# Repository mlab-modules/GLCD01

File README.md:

# GLCD01 - MIP LCD display module

MLAB module for the [TN0181ANVNANN-GN00](doc/datasheets/MIP_LCD.pdf) square MIP (Memory-in-Pixel) LCD display. MIP displays retain the image without power, making them suitable for low-power applications. The display is connected via a 10-pin FPC connector (J2) and communicates over a 3-wire SPI interface (SCLK, SI, SCS).

The module includes a [MIC1557](https://www.microchip.com/en-us/product/mic1557) RC oscillator that generates the required VCOM polarity-reversal signal for the LCD, so no external signal source is needed. Power supply is 3.3 V via the standard MLAB 2×7 pin header (J1).

## Design

## Schematics

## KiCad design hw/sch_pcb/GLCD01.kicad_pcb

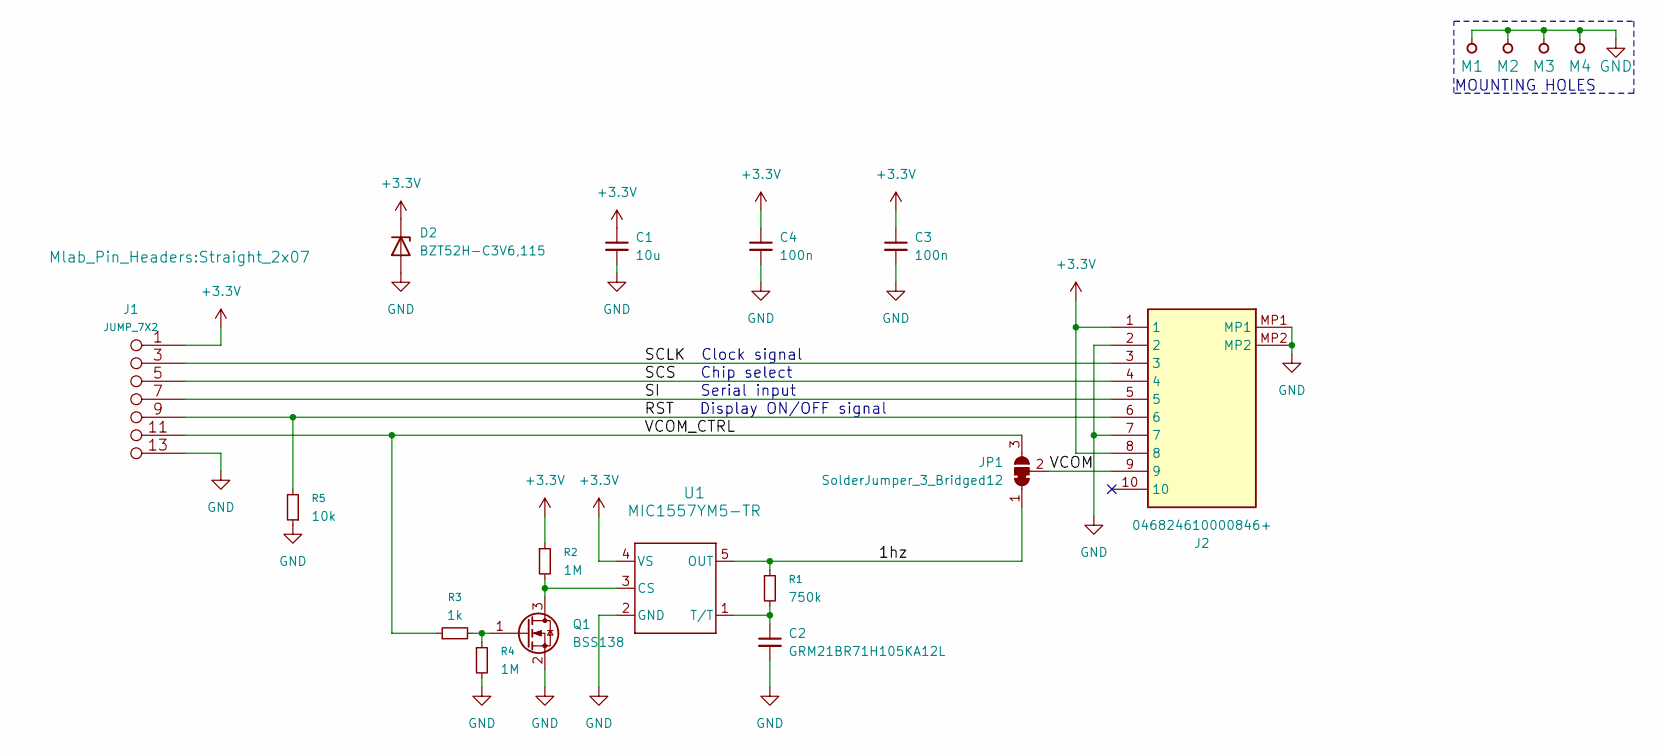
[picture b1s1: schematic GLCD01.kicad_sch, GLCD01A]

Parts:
C1: 10u; C_0603_1608Metric
C2: GRM21BR71H105KA12L; C_0603_1608Metric
C3, C4: 100n; C_0603_1608Metric
D2: BZT52H-C3V6,115; D_SOD-123F
J1: JUMP_7X2; Straight_2x07
J2: 046824610000846+; 046824610000846; Mouser Part Number 346-046824610000846
JP1: SolderJumper_3_Bridged12; SolderJumper-3_P1.3mm_Bridged12_RoundedPad1.0x1.5mm
M1, M2: HOLE M3; MountingHole_3mm
M3, M4: HOLE; MountingHole_3mm
Q1: BSS138; SOT-23
R1: 750k; R_0603_1608Metric
R2, R4: 1M; R_0603_1608Metric
R3: 1k; R_0603_1608Metric
R5: 10k; R_0603_1608Metric
U1: MIC1557YM5-TR; SOT-23-5

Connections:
+3.3V: C1.1, C3.1, C4.1, D2.1 (K), J1.1 (2), J1.2, J2.1, J2.8, R2.1, U1.4 (VS)
/1hz: JP1.1 (A), R1.1, U1.5 (OUT)
/RST: J1.9 (10), J1.10, J2.6, R5.2
/SCLK: J1.3 (4), J1.4, J2.3
/SCS: J1.5 (6), J1.6, J2.4
/SI: J1.7 (8), J1.8, J2.5
/VCOM: J2.9, JP1.2 (C)
/VCOM_CTRL: J1.11 (12), J1.12, JP1.3 (B), R3.1
GND: C1.2, C2.2, C3.2, C4.2, D2.2 (A), J1.13 (14), J1.14, J2.2, J2.7, J2.MP1, J2.MP2, M1.1, M2.1, M3.1, M4.1, Q1.2 (S), R4.2, R5.1, U1.2 (GND)
unnamed: Q1.3 (D), R2.2, U1.3 (CS)
unnamed: Q1.1 (G), R3.2, R4.1
unnamed: C2.1, R1.2, U1.1 (T/T)

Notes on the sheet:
Display ON/OFF signal
Clock signal
MOUNTING HOLES
Serial input
Chip select

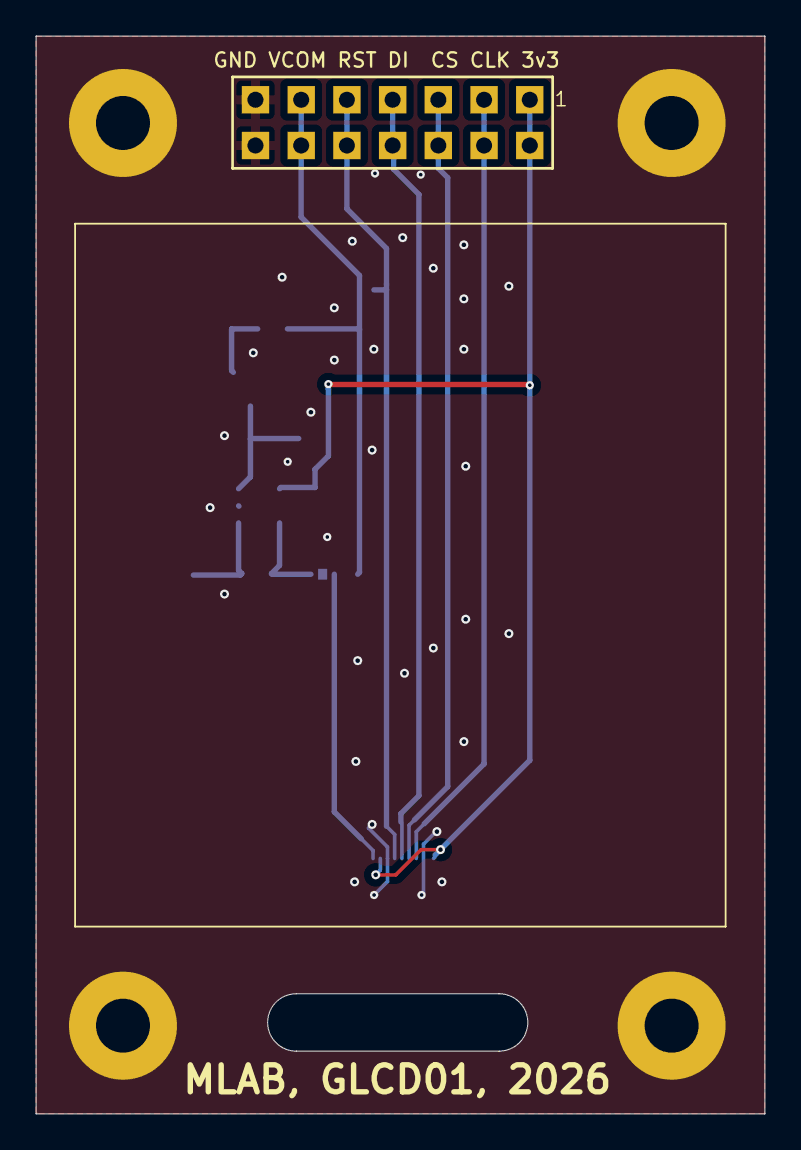
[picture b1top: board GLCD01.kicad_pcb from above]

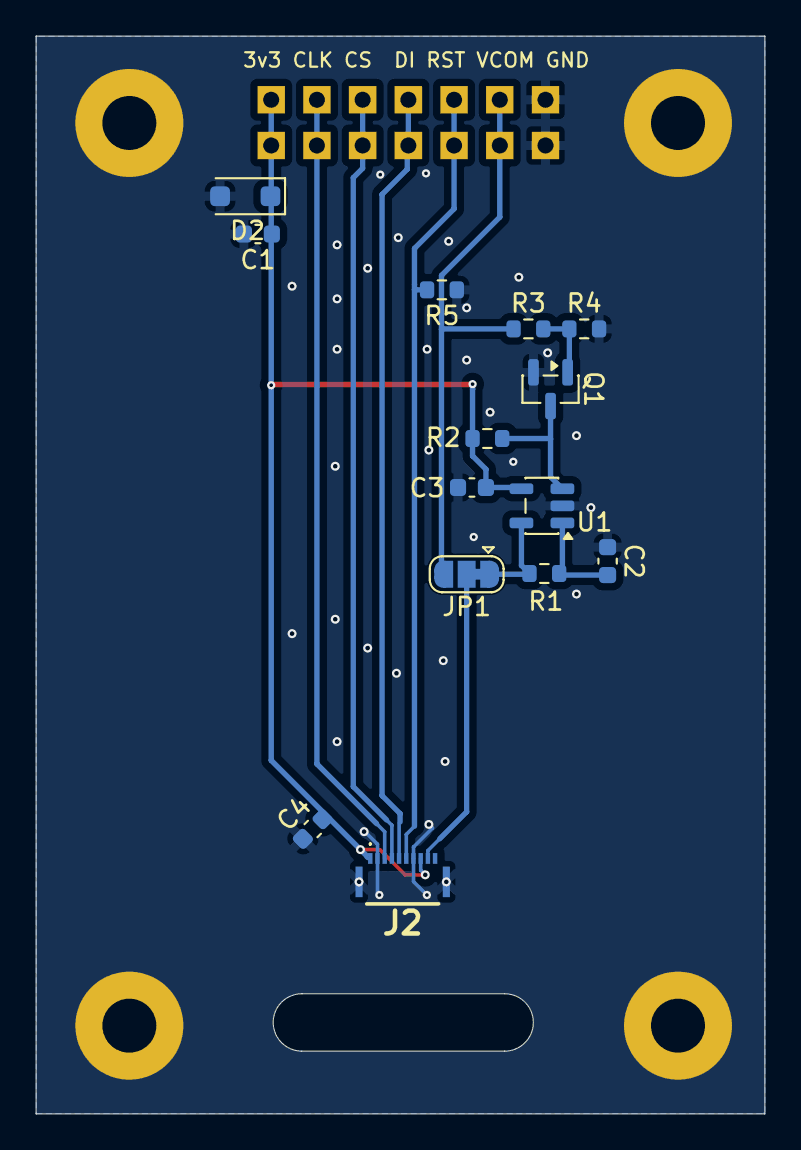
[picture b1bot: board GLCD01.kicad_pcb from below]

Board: 2 copper layers, 40.5 x 59.9 mm, 19 parts (14 on the bottom side), 12 nets.

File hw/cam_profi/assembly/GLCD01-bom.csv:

Component,Description,Part,References,Value,Footprint,Quantity Per PCB,Datasheet,height,mouser part number,mouser price/stock,manufacturer_name,manufacturer_part_number
1,"Unpolarized capacitor, small symbol",C_Small,C3C4,100nF/63V,C_0603_1608Metric,2,~,,,,,
2,GRM21BR71H105KA12L - nutno dodrzet typ,C_Small,C2,GRM21BR71H105KA12L,C_0603_1608Metric,1,~,,,,,
3,"10 Position FPC Connector Contacts, Top and Bottom 0.016"" (0.40mm) Surface Mount, Right Angle",046824610000846+,J2,046824610000846+,046824610000846,1,https://ele.kyocera.com/assets/products/connector/6824.pdf,1,346-046824610000846,https://www.mouser.co.uk/ProductDetail/KYOCERA-AVX/046824610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,Kyocera AVX,046824610000846+
4,MLAB modified doubled pinheader connector,JUMP_7X2,J1,JUMP_7X2,Straight_2x07,1,,,,,,
5,"50V Vds, 0.22A Id, N-Channel MOSFET, SOT-23",BSS138,Q1,BSS138,SOT-23,1,https://www.onsemi.com/pub/Collateral/BSS138-D.PDF,,,,,
6,"Resistor, small symbol",R_Small,R3,1k,R_0603_1608Metric,1,~,,,,,
7,"Resistor, small symbol",R_Small,R1,750k,R_0603_1608Metric,1,~,,,,,
8,"Resistor, small symbol",R_Small,R2R4,1M,R_0603_1608Metric,2,~,,,,,
9,,MIC1557YM5-TR,U1,MIC1557YM5-TR,SOT-23-5,1,MIC1557YM5-TR,,,,,

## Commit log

2026-02-28 Update workflow files
2026-02-28 Update metadata files
2026-02-28 Initial KiCAD project template commit.
2026-02-28 Automatic update of KiCAD outputs
2026-03-18 v1 with mic1557
2026-05-06 Add MIC1557 circuit to schematic and update PCB layout
    - Added R5 (0R, DNP) resistor to schematic
    - Rearranged component placement on PCB
    - Updated project file to newer KiCAD format
    - Fixed author email in schematic title block
2026-05-06 Update PCB layout and tighten DRC rules
    Reduced clearance and hole constraints for denser routing.
2026-05-11 fix schematics, improve layout, thicker traces, update layout, add polarity protection, ...
2026-05-11 readme, text to schematics
2026-05-11 readme
